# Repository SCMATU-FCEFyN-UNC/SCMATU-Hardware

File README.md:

# SCMATU-Hardware
Hardware design for the thesis project "SCMATU," developed to excite and measure PZT ultrasonic transducers for automatic resonance frequency determination. The system provides a controlled sinusoidal excitation stage (±10 V), voltage and current sensing circuitry, and signal conditioning to enable accurate phase measurement between voltage and current during frequency sweeps.

---

## Repository Initialization

To obtain this repository locally, use the following commands:

### 1. Initialize Local Repository

```bash
cd your_local_directory
git init
```

### 2. Mark Directory as Safe (If Required)

Some environments may require explicitly marking the repository as safe.

- Bash (Git Bash, WSL, macOS Terminal, Linux):

```bash
git config --global --add safe.directory "$(pwd)"
```

- PowerShell:

```powershell
git config --global --add safe.directory "%cd%"
```

### 3. Add Remote Repository and Pull Branches

```bash
git remote add origin https://github.com/SCMATU-FCEFyN-UNC/SCMATU-Hardware.git
git pull origin main
```

> KiCad v7.0 or later is recommended to open the project files.

---

## 📄 Documentation

- [Schematic](docs/Complete_Schematic.pdf)
- [Hardware Requirements Specification](docs/requirements.md)

---

# License

This project is licensed under the MIT License.

See the [LICENSE](LICENSE) file for full license text.

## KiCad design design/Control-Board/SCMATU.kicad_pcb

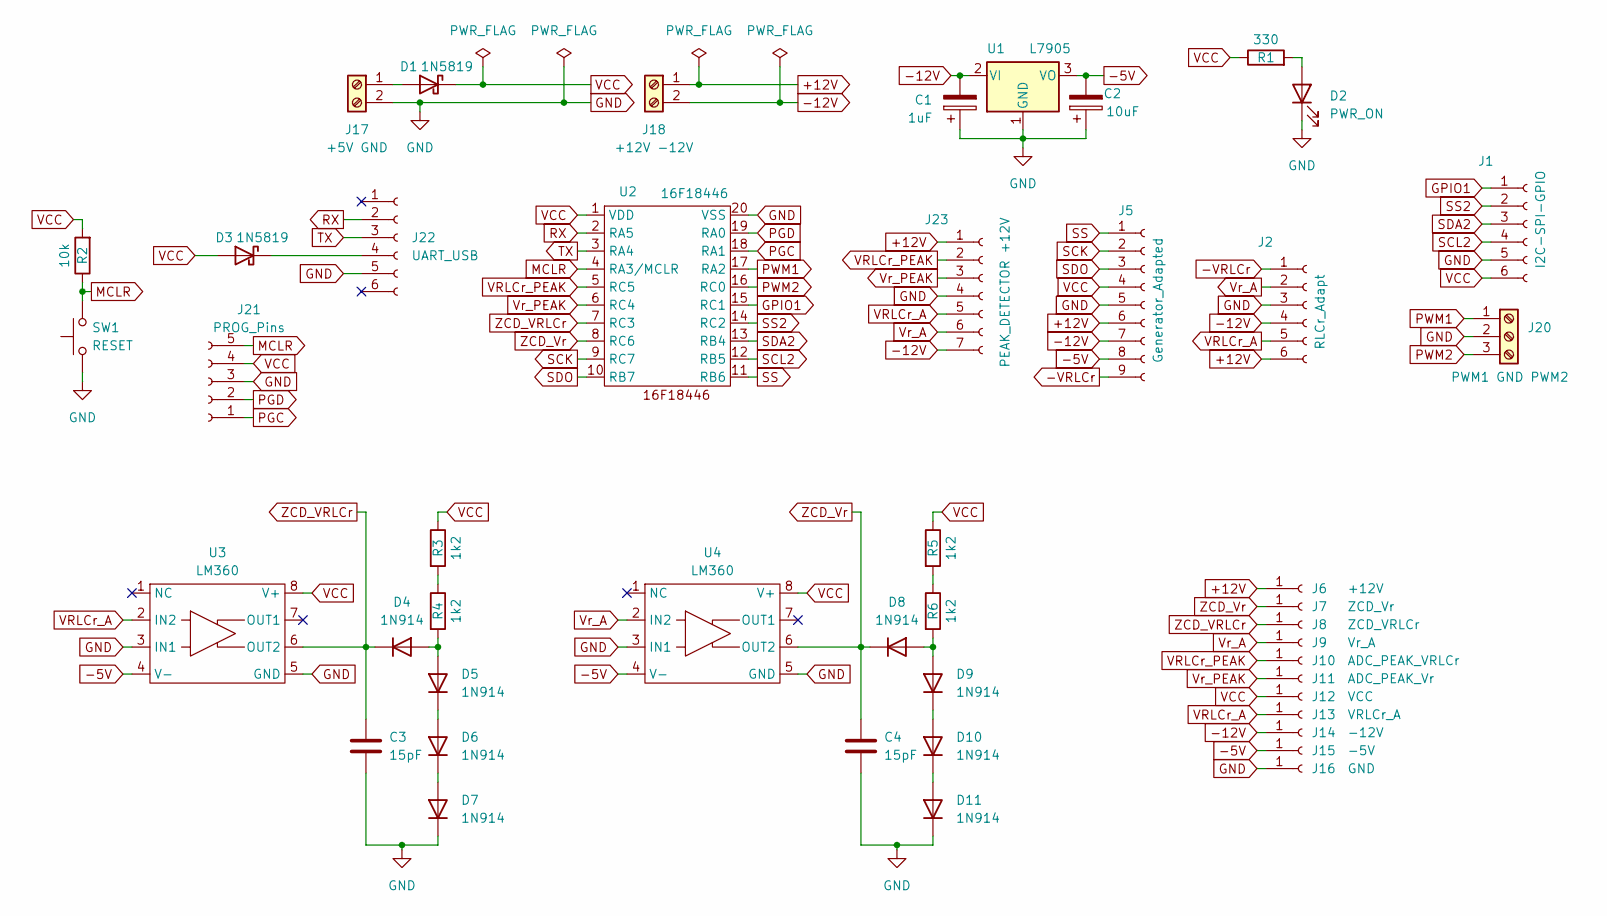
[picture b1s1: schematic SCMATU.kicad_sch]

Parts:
C1: 1uF; CP_Radial_D5.0mm_P2.00mm
C2: 10uF; CP_Radial_D5.0mm_P2.00mm
C3, C4: 15pF; C_Disc_D5.0mm_W2.5mm_P2.50mm
D1, D3: 1N5819; D_DO-41_SOD81_P10.16mm_Horizontal
D2: PWR_ON; LED_D5.0mm_IRGrey
D4, D5, D6, D7, D8, D9, D10, D11: 1N914; D_DO-35_SOD27_P7.62mm_Horizontal
J1: I2C-SPI-GPIO; PinHeader_1x06_P2.54mm_Vertical
J2: RLCr_Adapt; PinHeader_1x06_P2.54mm_Vertical
J5: Generator_Adapted; PinHeader_1x09_P2.54mm_Vertical
J6: +12V; PinHeader_1x01_P2.54mm_Vertical
J7: ZCD_Vr; PinHeader_1x01_P2.54mm_Vertical
J8: ZCD_VRLCr; PinHeader_1x01_P2.54mm_Vertical
J9: Vr_A; PinHeader_1x01_P2.54mm_Vertical
J10: ADC_PEAK_VRLCr; PinHeader_1x01_P2.54mm_Vertical
J11: ADC_PEAK_Vr; PinHeader_1x01_P2.54mm_Vertical
J12: VCC; PinHeader_1x01_P2.54mm_Vertical
J13: VRLCr_A; PinHeader_1x01_P2.54mm_Vertical
J14: -12V; PinHeader_1x01_P2.54mm_Vertical
J15: -5V; PinHeader_1x01_P2.54mm_Vertical
J16: GND; TestPoint_Pad_10.0x10.0mm
J17: +5V GND; TerminalBlock_Plug_Bornier-2-P5.08mm
J18: +12V -12V; TerminalBlock_Plug_Bornier-2-P5.08mm
J20: PWM1 GND PWM2; PinHeader_1x03_P2.54mm_Vertical
J21: PROG_Pins; PinHeader_1x05_P2.54mm_Vertical
J22: UART_USB; PinHeader_1x06_P2.54mm_Horizontal
J23: PEAK_DETECTOR +12V; PinHeader_1x07_P2.54mm_Vertical
R1: 330; R_Axial_DIN0207_L6.3mm_D2.5mm_P10.16mm_Horizontal
R2: 10k; R_Axial_DIN0207_L6.3mm_D2.5mm_P10.16mm_Horizontal
R3, R4, R5, R6: 1k2; R_Axial_DIN0207_L6.3mm_D2.5mm_P10.16mm_Horizontal
SW1: RESET; SW_PUSH_6mm
U1: L7905; TO-220-3_Vertical
U2: 16F18446; SOIC-20W_7.5x12.8mm_P1.27mm
U3, U4: LM360; DIP-8_W7.62mm_Socket_LongPads

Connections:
+12V: J2.6, J5.6, J6.1, J18.1, J23.1
-5V: C2.2, J5.8, J15.1, U1.3 (VO), U3.4 (V-), U4.4 (V-)
-12V: C1.2, J2.4, J5.7, J14.1, J18.2, J23.7, U1.2 (VI)
-VRLCr: J2.1, J5.9
GND: C1.1, C2.1, C3.2, C4.2, D2.1 (K), D7.1 (K), D11.1 (K), J1.5, J2.3, J5.5, J16.1, J17.2, J20.2, J21.3, J22.5, J23.4, SW1.1, U1.1 (GND), U2.20 (VSS), U3.3 (IN1), U3.5 (GND), U4.3 (IN1), U4.5 (GND)
GPIO1: J1.1, U2.15 (RC1)
MCLR: J21.5, R2.1, SW1.2, U2.4 (RA3/MCLR)
unnamed: D1.2 (A), J17.1
unnamed: D2.2 (A), R1.2
unnamed: D3.1 (K), J22.4
unnamed: D4.2 (A), D5.2 (A), R4.2
unnamed: D5.1 (K), D6.2 (A)
unnamed: D6.1 (K), D7.2 (A)
unnamed: D8.2 (A), D9.2 (A), R6.2
unnamed: D9.1 (K), D10.2 (A)
unnamed: D10.1 (K), D11.2 (A)
unnamed: R3.2, R4.1
unnamed: R5.2, R6.1
PGC: J21.1, U2.18 (RA1)
PGD: J21.2, U2.19 (RA0)
PWM1: J20.1, U2.17 (RA2)
PWM2: J20.3, U2.16 (RC0)
RX: J22.2, U2.2 (RA5)
SCK: J5.2, U2.9 (RC7)
SCL2: J1.4, U2.12 (RB5)
SDA2: J1.3, U2.13 (RB4)
SDO: J5.3, U2.10 (RB7)
SS: J5.1, U2.11 (RB6)
SS2: J1.2, U2.14 (RC2)
TX: J22.3, U2.3 (RA4)
VCC: D1.1 (K), D3.2 (A), J1.6, J5.4, J12.1, J21.4, R1.1, R2.2, R3.1, R5.1, U2.1 (VDD), U3.8 (V+), U4.8 (V+)
VRLCr_A: J2.5, J13.1, J23.5, U3.2 (IN2)
VRLCr_PEAK: J10.1, J23.2, U2.5 (RC5)
Vr_A: J2.2, J9.1, J23.6, U4.2 (IN2)
Vr_PEAK: J11.1, J23.3, U2.6 (RC4)
ZCD_VRLCr: C3.1, D4.1 (K), J8.1, U2.7 (RC3), U3.6 (OUT2)
ZCD_Vr: C4.1, D8.1 (K), J7.1, U2.8 (RC6), U4.6 (OUT2)

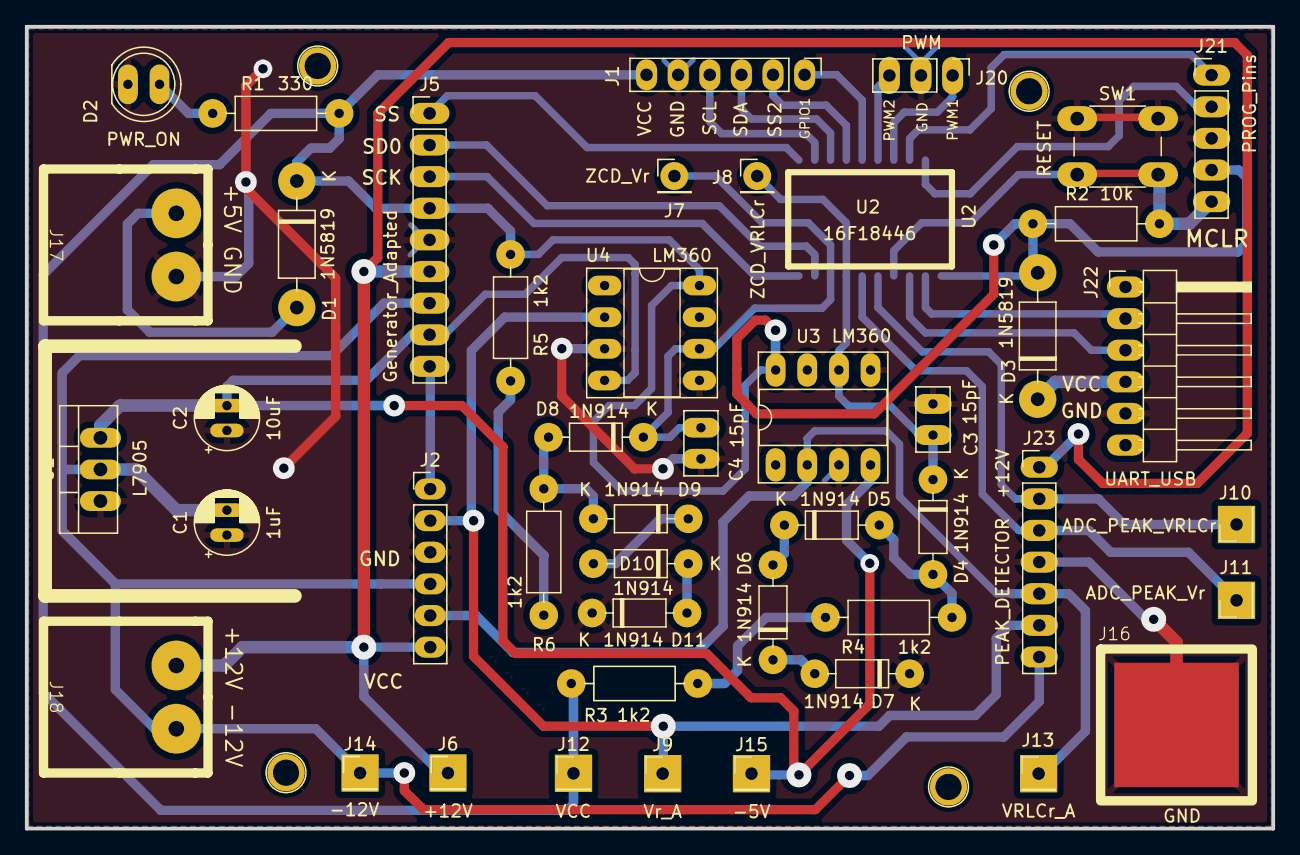
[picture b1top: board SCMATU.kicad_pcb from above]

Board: 2 copper layers, 100.1 x 64.4 mm, 46 parts (1 on the bottom side), 37 nets.

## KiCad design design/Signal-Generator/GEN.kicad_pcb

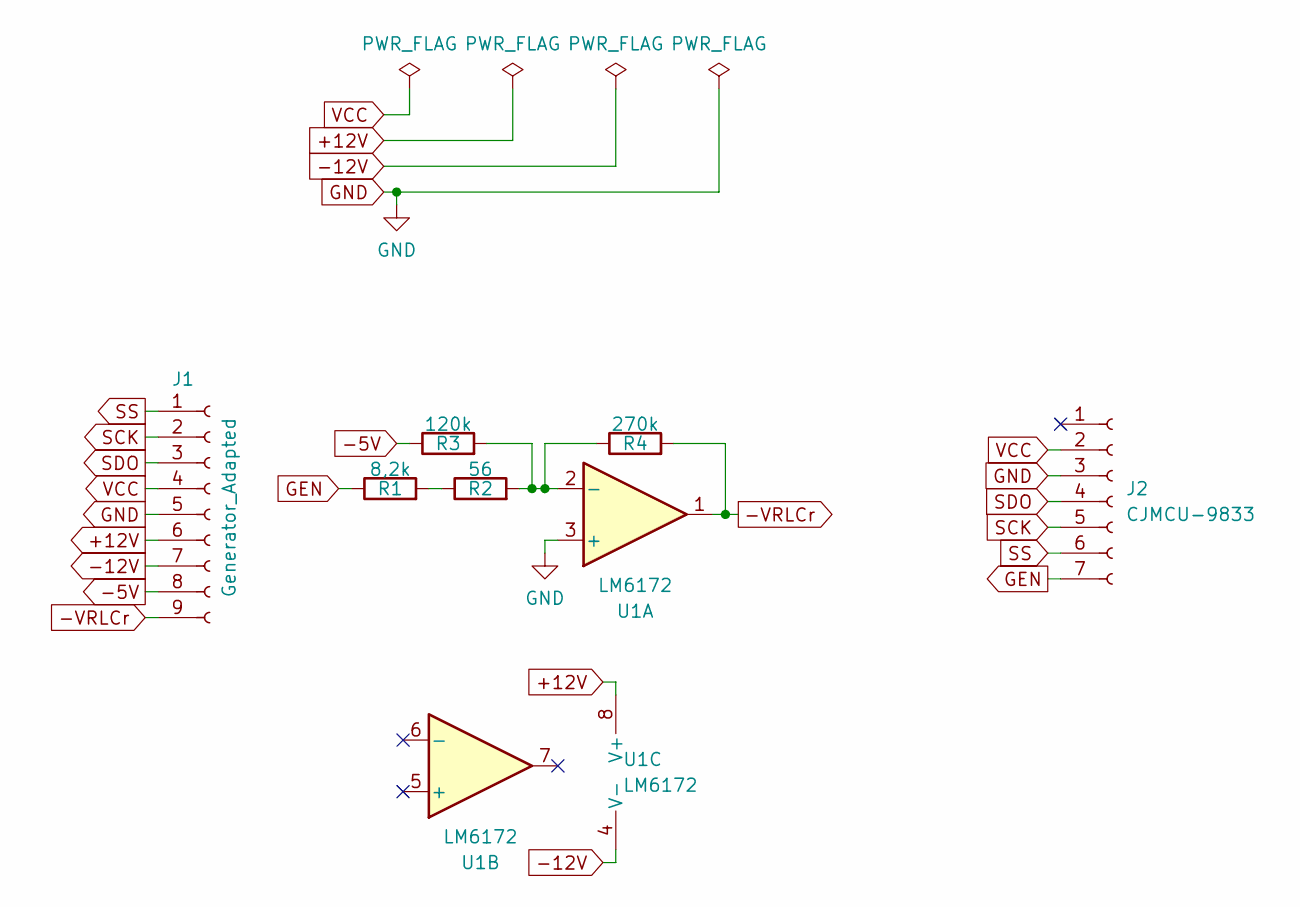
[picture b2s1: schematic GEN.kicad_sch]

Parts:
J1: Generator_Adapted; PinHeader_1x09_P2.54mm_Vertical
J2: CJMCU-9833; PinHeader_1x07_P2.54mm_Horizontal
R1: 8,2k; R_Axial_DIN0207_L6.3mm_D2.5mm_P10.16mm_Horizontal
R2: 56; R_Axial_DIN0207_L6.3mm_D2.5mm_P10.16mm_Horizontal
R3: 120k; R_Axial_DIN0207_L6.3mm_D2.5mm_P10.16mm_Horizontal
R4: 270k; R_Axial_DIN0207_L6.3mm_D2.5mm_P10.16mm_Horizontal
U1: LM6172; DIP-8_W7.62mm_Socket_LongPads

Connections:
+12V: J1.6, U1.8 (V+)
-5V: J1.8, R3.1
-12V: J1.7, U1.4 (V-)
-VRLCr: J1.9, R4.2, U1.1
GEN: J2.7, R1.1
GND: J1.5, J2.3, U1.3 (+)
unnamed: R1.2, R2.1
unnamed: R2.2, R3.2, R4.1, U1.2 (-)
SCK: J1.2, J2.5
SDO: J1.3, J2.4
SS: J1.1, J2.6
VCC: J1.4, J2.2

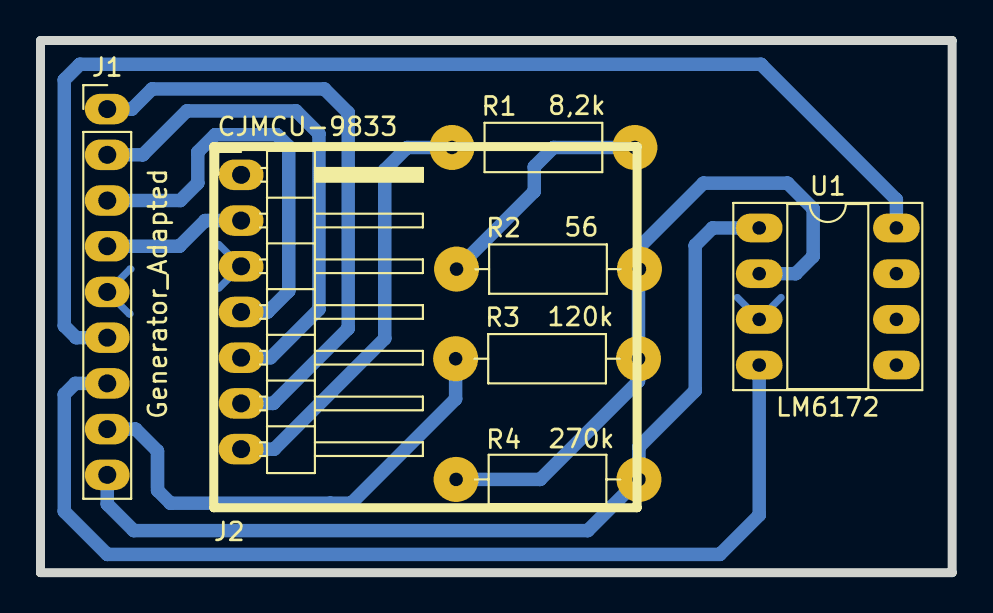
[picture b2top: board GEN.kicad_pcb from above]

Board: 2 copper layers, 50.6 x 29.6 mm, 7 parts (0 on the bottom side), 12 nets.

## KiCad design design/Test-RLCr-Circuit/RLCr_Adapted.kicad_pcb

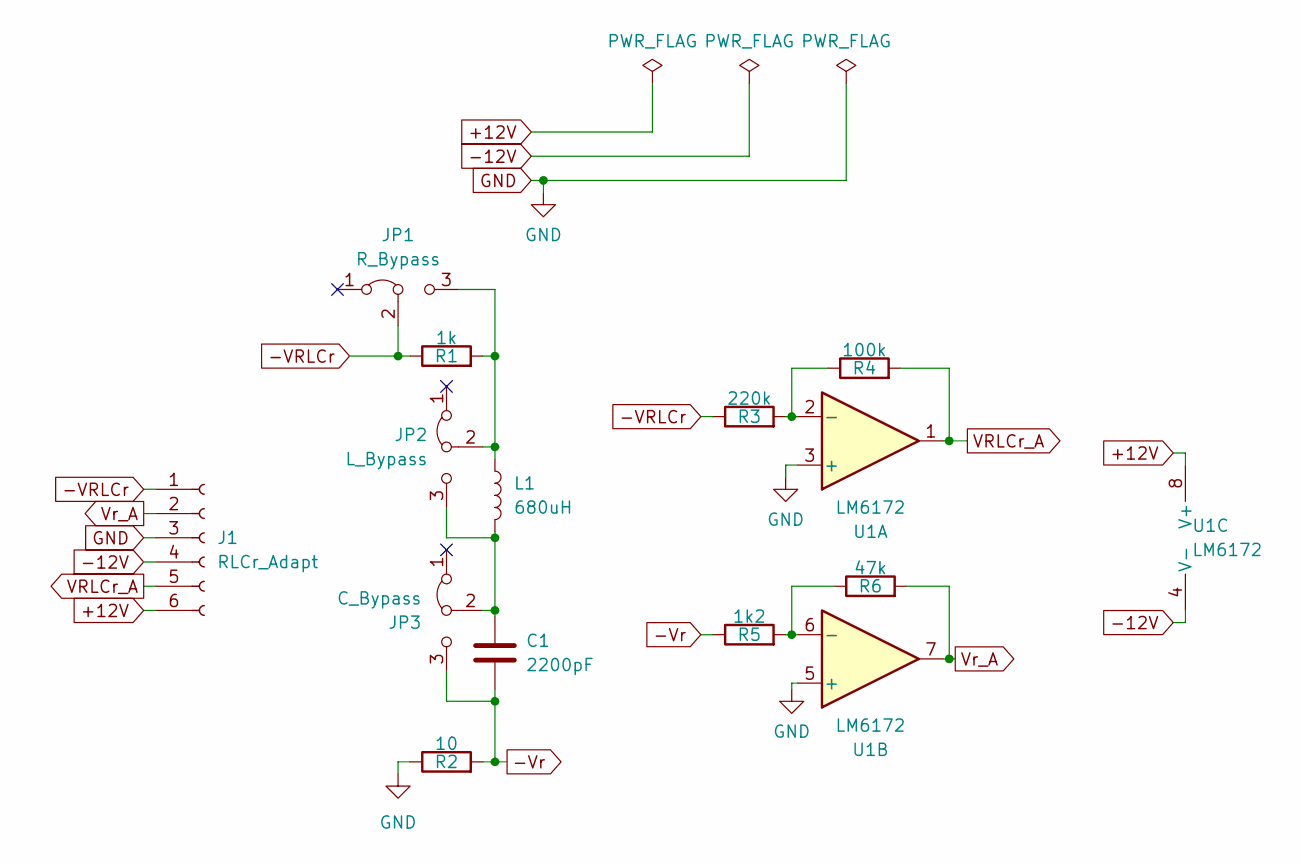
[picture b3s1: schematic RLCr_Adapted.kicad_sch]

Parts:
C1: 2200pF; C_Disc_D5.0mm_W2.5mm_P2.50mm
J1: RLCr_Adapt; PinHeader_1x06_P2.54mm_Vertical
JP1: R_Bypass; PinHeader_1x03_P2.54mm_Vertical
JP2: L_Bypass; PinHeader_1x03_P2.54mm_Vertical
JP3: C_Bypass; PinHeader_1x03_P2.54mm_Vertical
L1: 680uH; L_Axial_L7.0mm_D3.3mm_P10.16mm_Horizontal_Fastron_MICC
R1: 1k; R_Axial_DIN0207_L6.3mm_D2.5mm_P10.16mm_Horizontal
R2: 10; R_Axial_DIN0207_L6.3mm_D2.5mm_P10.16mm_Horizontal
R3: 220k; R_Axial_DIN0207_L6.3mm_D2.5mm_P10.16mm_Horizontal
R4: 100k; R_Axial_DIN0207_L6.3mm_D2.5mm_P10.16mm_Horizontal
R5: 1k2; R_Axial_DIN0207_L6.3mm_D2.5mm_P10.16mm_Horizontal
R6: 47k; R_Axial_DIN0207_L6.3mm_D2.5mm_P10.16mm_Horizontal
U1: LM6172; DIP-8_W7.62mm_Socket_LongPads

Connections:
+12V: J1.6, U1.8 (V+)
-12V: J1.4, U1.4 (V-)
-VRLCr: J1.1, JP1.2 (C), R1.1, R3.1
-Vr: C1.2, JP3.3 (B), R2.2, R5.1
GND: J1.3, R2.1, U1.3 (+), U1.5 (+)
unnamed: JP1.3 (B), JP2.2 (C), L1.1, R1.2
unnamed: C1.1, JP2.3 (B), JP3.2 (C), L1.2
unnamed: R3.2, R4.1, U1.2 (-)
unnamed: R5.2, R6.1, U1.6 (-)
VRLCr_A: J1.5, R4.2, U1.1
Vr_A: J1.2, R6.2, U1.7

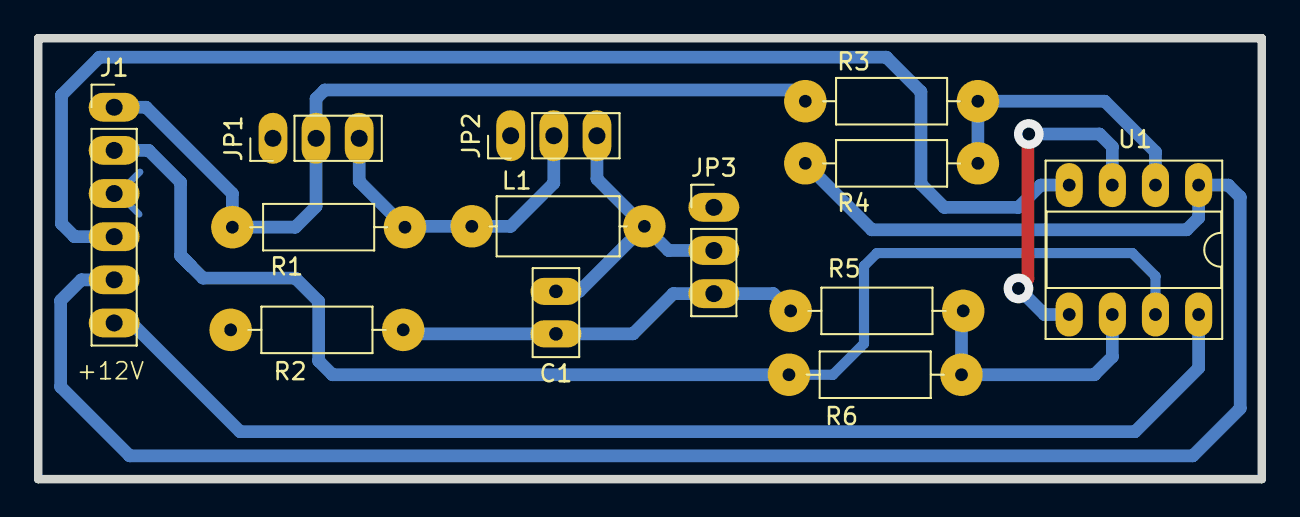
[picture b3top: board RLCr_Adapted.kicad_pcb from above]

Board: 2 copper layers, 72.0 x 26.0 mm, 13 parts (0 on the bottom side), 11 nets.

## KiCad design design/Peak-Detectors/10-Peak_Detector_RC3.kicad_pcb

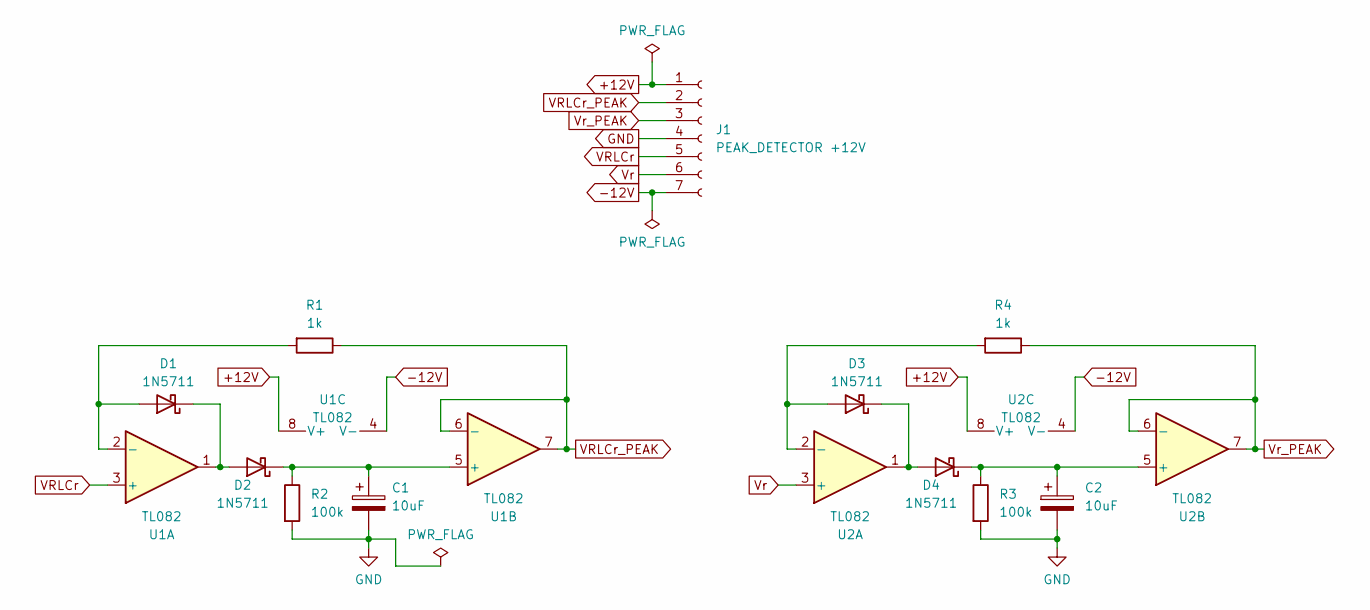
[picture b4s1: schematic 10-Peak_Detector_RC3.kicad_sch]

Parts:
C1, C2: 10uF; CP_Radial_D5.0mm_P2.00mm
D1, D2, D3, D4: 1N5711; D_DO-35_SOD27_P7.62mm_Horizontal
J1: PEAK_DETECTOR +12V; PinHeader_1x07_P2.54mm_Vertical
R1, R4: 1k; R_Axial_DIN0207_L6.3mm_D2.5mm_P7.62mm_Horizontal
R2, R3: 100k; R_Axial_DIN0207_L6.3mm_D2.5mm_P7.62mm_Horizontal
U1, U2: TL082; DIP-8_W7.62mm_Socket_LongPads

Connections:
+12V: J1.1, U1.8 (V+), U2.8 (V+)
-12V: J1.7, U1.4 (V-), U2.4 (V-)
GND: C1.2, C2.2, J1.4, R2.2, R3.2
unnamed: D1.2 (A), R1.2, U1.2 (-)
unnamed: D1.1 (K), D2.2 (A), U1.1
unnamed: C1.1, D2.1 (K), R2.1, U1.5 (+)
unnamed: D3.2 (A), R4.2, U2.2 (-)
unnamed: D3.1 (K), D4.2 (A), U2.1
unnamed: C2.1, D4.1 (K), R3.1, U2.5 (+)
VRLCr: J1.5, U1.3 (+)
VRLCr_PEAK: J1.2, R1.1, U1.6 (-), U1.7
Vr: J1.6, U2.3 (+)
Vr_PEAK: J1.3, R4.1, U2.6 (-), U2.7

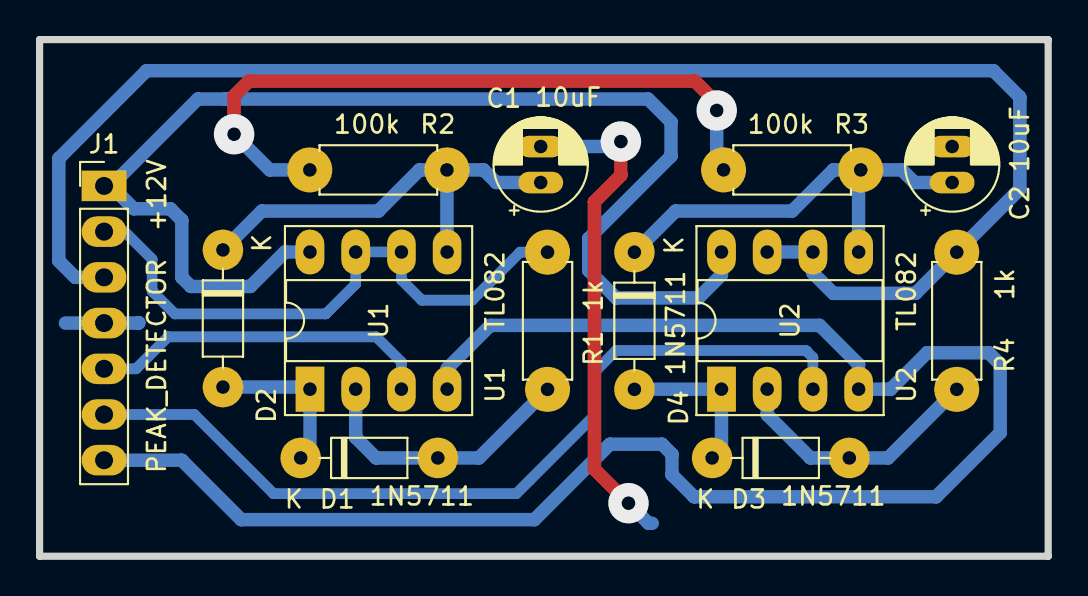
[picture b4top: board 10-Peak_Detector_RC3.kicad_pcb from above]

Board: 2 copper layers, 56.0 x 28.7 mm, 13 parts (0 on the bottom side), 13 nets.

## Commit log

2026-02-25 chore(repo-config-and-docs): README and .gitignore
2026-02-25 Upload PCB design, outputs and full shematic
2026-02-25 chore: Minor README adjustment
